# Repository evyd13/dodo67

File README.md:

# Dodo67 PCB

## Daughterboard

Check out the daughterboard under `daughterboard/`.

## PCB
The Dodo67 PCB will be uploaded later.

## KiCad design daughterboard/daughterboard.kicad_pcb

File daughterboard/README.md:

# Dodo67 Daughterboard

## Same direction? Reverse direction...?
Please read this blog post: [anykeys.eu/post/jst-cables...](https://web.archive.org/web/20220301022901/https://anykeys.eu/post/jst-cables-and-daughterboards/)

In essence: the original Doro67 PCB needs a 'same direction' cable, while the Dodo67 PCB needs a 'reverse direction' cable. This is because the Unified Daughterboard specification uses the latter.

***HOWEVER, the first version of the Dodo67 PCB, which was sold by MyKeyboard, uses a reverse direction cable.***

## What's the hole for?
The hole next to the breakout pins (which you can solder a wire to) is for cable relief! Use a zip tie to secure it to the daughterboard and prevent it from moving around.

## A note on PCB thickness
This daughterboard is intended to be 2.0mm thick. This is so you don't need the washers like the original Dodo67 daughterboard did. You can use it in 1.6mm as well, but remember to use the washers in that case!

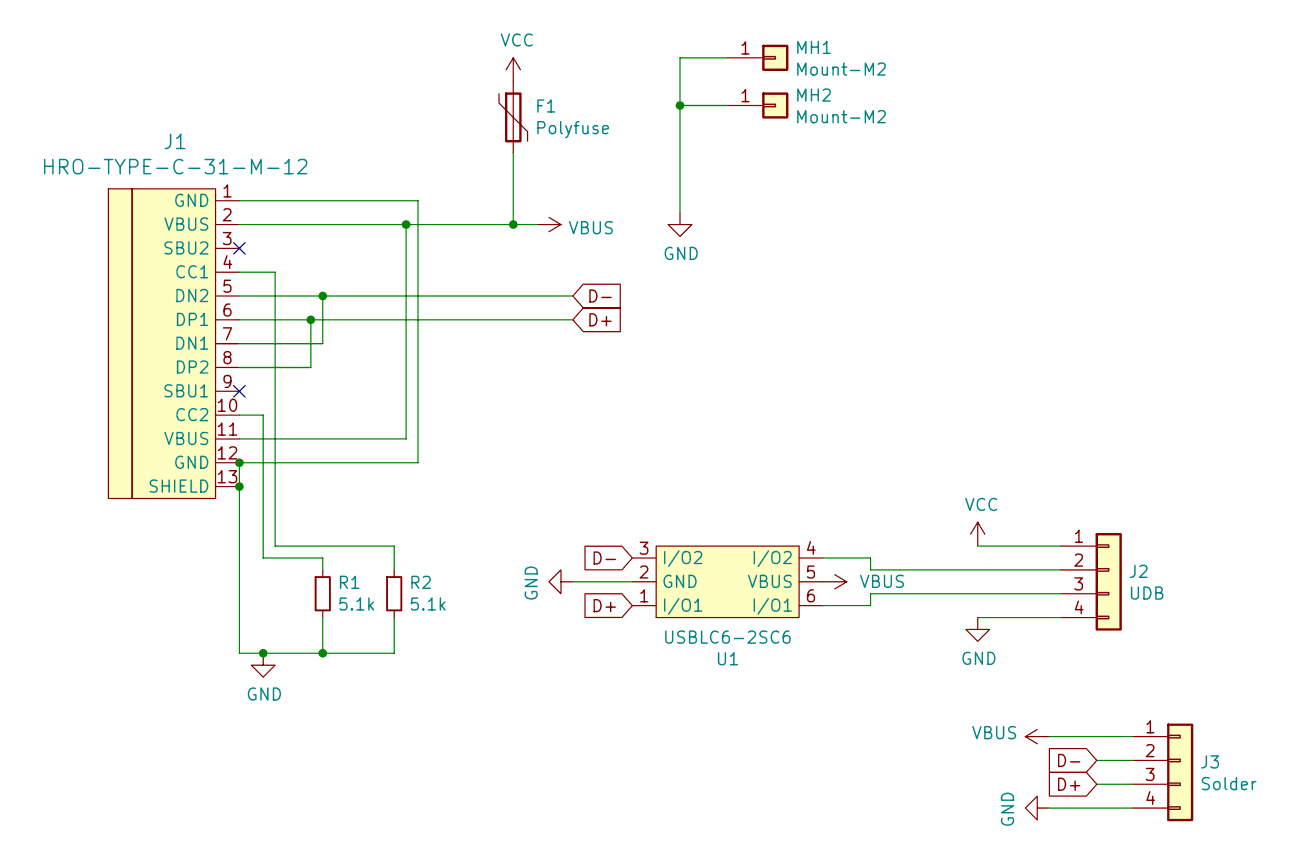
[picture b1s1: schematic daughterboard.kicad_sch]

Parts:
F1: Polyfuse; R_0805
J1: HRO-TYPE-C-31-M-12; CONN_HRO-TYPE-C-31-M-12
J2: UDB; CONN_JST_SH_SM04B-SRSS-TB_1x04-1MP_P1.00mm_Horizontal
J3: Solder; solder_header
MH1, MH2: Mount-M2; 3x2.2
R1, R2: 5.1k; R_0805
U1: USBLC6-2SC6; PACKAGE_SOT-23-6; Farnell 1295310

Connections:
D+: J1.6 (DP1), J1.8 (DP2), J3.3, U1.1 (I/O1)
D-: J1.5 (DN2), J1.7 (DN1), J3.2, U1.3 (I/O2)
GND: J1.1 (GND), J1.12 (GND), J1.13 (SHIELD), J2.4, J3.4, MH1.1, MH2.1, R1.2, R2.2, U1.2 (GND)
unnamed: J1.4 (CC1), R2.1
unnamed: J1.10 (CC2), R1.1
unnamed: J2.2, U1.4 (I/O2)
unnamed: J2.3, U1.6 (I/O1)
VBUS: F1.2, J1.2 (VBUS), J1.11 (VBUS), J3.1, U1.5 (VBUS)
VCC: F1.1, J2.1

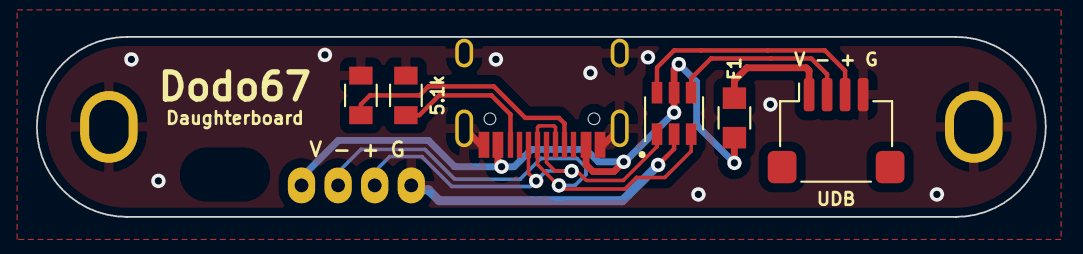
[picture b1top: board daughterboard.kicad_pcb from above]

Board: 2 copper layers, 56.1 x 10.0 mm, 9 parts (0 on the bottom side), 9 nets.

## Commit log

2022-03-01 Upload daughterboard files
2022-03-01 Quick, edit the readme so they don't notice
2022-03-01 Add license
2022-03-10 upload pcb
